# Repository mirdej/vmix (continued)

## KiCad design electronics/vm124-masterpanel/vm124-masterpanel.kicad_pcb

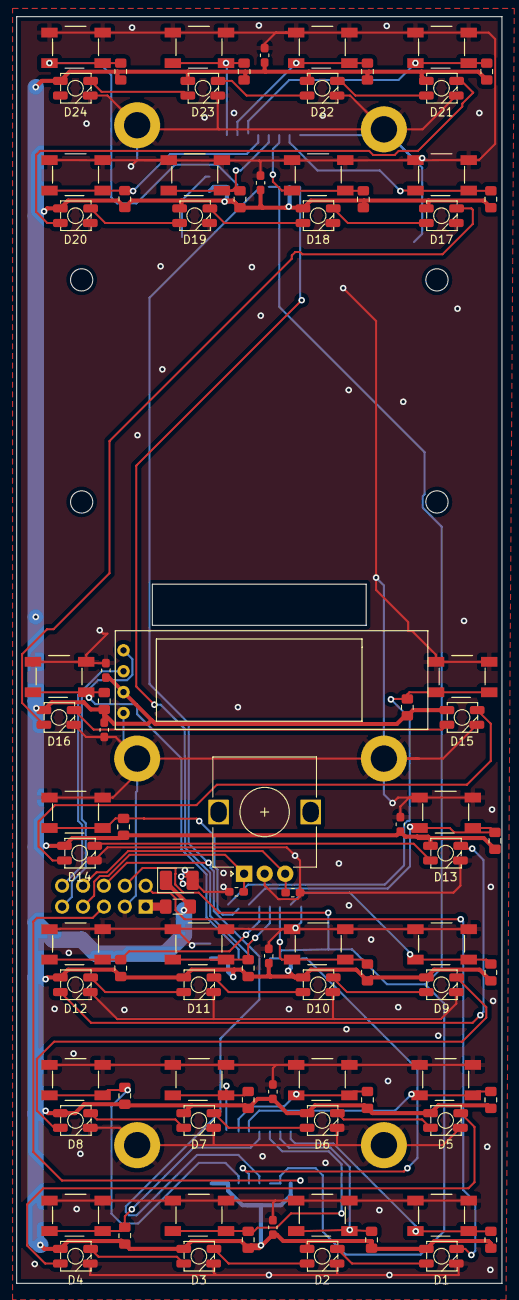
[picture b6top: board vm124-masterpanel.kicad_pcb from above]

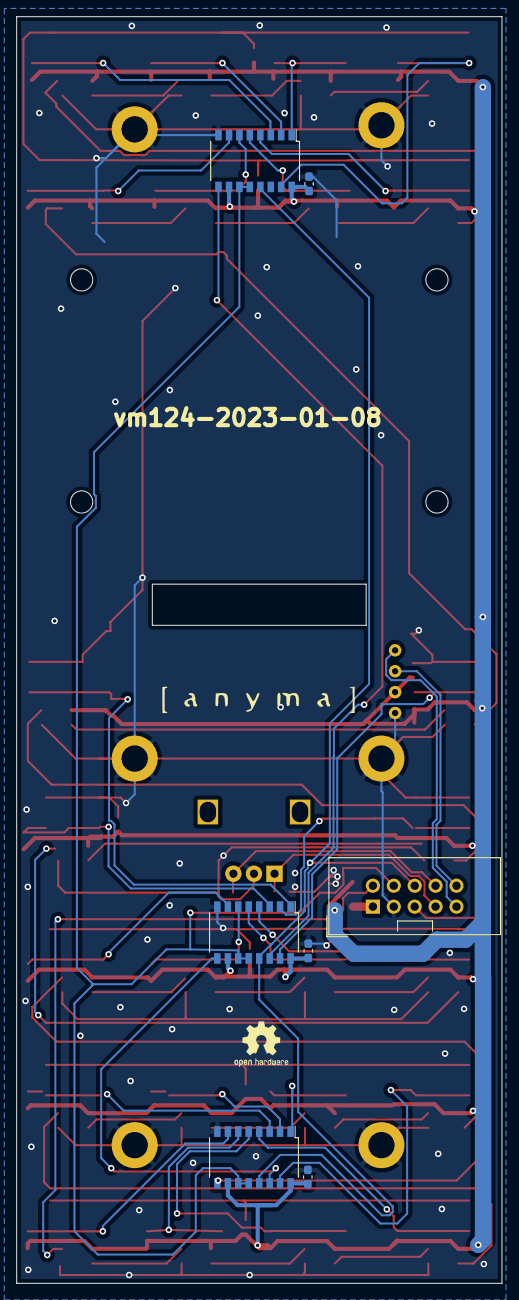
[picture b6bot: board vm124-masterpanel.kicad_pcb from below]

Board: 2 copper layers, 59.0 x 154.0 mm, 105 parts (9 on the bottom side), 60 nets.

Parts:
C1, C2, C3, C5, C6, C7, C8, C12, C13, C201, C202: C; C_0603_1608Metric_Pad1.05x0.95mm_HandSolder
C101: CP; CP_EIA-3528-21_Kemet-B_Pad1.50x2.35mm_HandSolder
C102, C103: 100n; C_0603_1608Metric_Pad1.05x0.95mm_HandSolder
D1, D2, D3, D4, D5, D6, D7, D8, D9, D10, D11, D12, D13, D14, D15, D16, D17, D18, D19, D20, D21, D22, D23, D24: SK6812MINI; SK6812-MINI-HS
FB101: Ferrite_Bead; L_1206_3216Metric_Pad1.42x1.75mm_HandSolder
H4, H5, H6, H7, H8, H9: MountingHole_Pad; MountingHole_3.2mm_M3_DIN965_Pad
H101, H102, H103, H104: MountingHole; MountingHole_2.7mm_M2.5
J101: Display; Bangood-OLED-128x32
J102: To-CPU; IDC-Header_2x05_P2.54mm_Vertical
R5, R6, R7, R8, R9, R10, R11, R12, R13, R14, R15, R16, R17, R18, R19, R20, R29, R30, R31, R32, R33, R34, R35, R36: R; R_0805_2012Metric_Pad1.15x1.40mm_HandSolder
SW5, SW6, SW7, SW8, SW9, SW10, SW11, SW12, SW13, SW14, SW15, SW16, SW17, SW18, SW19, SW20, SW29, SW30, SW31, SW32, SW33, SW34, SW35, SW36: SW_Push; Alps_Tactile_Switch
SW101: Rotary_Encoder; RotaryEncoder_Alps_EC12E_Vertical_H20mm
U2, U3, U5: 74LS597; SOP-16_4.4x10.4mm_P1.27mm
U101: LOGO; logo_anyma
U102: LOGO; OSHW-Logo2_7.3x6mm_SilkScreen

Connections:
/enc_a: C102.1, J102.7, SW101.A
/enc_b: C103.1, J102.8, SW101.B
/scl: J101.3, J102.10
/sda: J101.4, J102.9
GND: C1.2, C2.2, C3.2, C5.2, C6.2, C7.2, C8.2, C12.2, C13.2, C101.2, C102.2, C103.2, C201.2, C202.2, D1.2 (VSS), D2.2 (VSS), D3.2 (VSS), D4.2 (VSS), D5.2 (VSS), D6.2 (VSS), D7.2 (VSS), D8.2 (VSS), D9.2 (VSS), D10.2 (VSS), D11.2 (VSS), D12.2 (VSS), D13.2 (VSS), D14.2 (VSS), D15.2 (VSS), D16.2 (VSS), D17.2 (VSS), D18.2 (VSS), D19.2 (VSS), D20.2 (VSS), D21.2 (VSS), D22.2 (VSS), D23.2 (VSS), D24.2 (VSS), H4.1, H5.1, H6.1, H7.1, H8.1, H9.1, J101.1, J102.3, SW5.1, SW6.1, SW7.1, SW8.1, SW9.1, SW10.1, SW11.1, SW12.1, SW13.1, SW14.1, SW15.1, SW16.1, SW17.1, SW18.1, SW19.1, SW20.1, SW29.1, SW30.1, SW31.1, SW32.1, SW33.1, SW34.1, SW35.1, SW36.1, SW101.C, U2.8 (GND), U3.8 (GND), U5.8 (GND)
unnamed: D1.1 (DOUT), D2.3 (DIN)
unnamed: D2.1 (DOUT), D3.3 (DIN)
unnamed: D3.1 (DOUT), D4.3 (DIN)
unnamed: D4.1 (DOUT), D5.3 (DIN)
unnamed: D5.1 (DOUT), D6.3 (DIN)
unnamed: D6.1 (DOUT), D7.3 (DIN)
unnamed: D7.1 (DOUT), D8.3 (DIN)
unnamed: D8.1 (DOUT), D9.3 (DIN)
unnamed: D10.1 (DOUT), D11.3 (DIN)
unnamed: D9.1 (DOUT), D10.3 (DIN)
unnamed: D11.1 (DOUT), D12.3 (DIN)
unnamed: D12.1 (DOUT), D13.3 (DIN)
unnamed: D13.1 (DOUT), D14.3 (DIN)
unnamed: D14.1 (DOUT), D15.3 (DIN)
unnamed: D15.1 (DOUT), D16.3 (DIN)
unnamed: D16.1 (DOUT), D17.3 (DIN)
unnamed: D17.1 (DOUT), D18.3 (DIN)
unnamed: D18.1 (DOUT), D19.3 (DIN)
unnamed: D19.1 (DOUT), D20.3 (DIN)
unnamed: D20.1 (DOUT), D21.3 (DIN)
unnamed: D21.1 (DOUT), D22.3 (DIN)
unnamed: D22.1 (DOUT), D23.3 (DIN)
unnamed: D23.1 (DOUT), D24.3 (DIN)
unnamed: FB101.2, J102.1
unnamed: R5.2, SW5.2, U2.15 (A)
unnamed: R6.2, SW6.2, U2.1 (B)
unnamed: R7.2, SW7.2, U2.2 (C)
unnamed: R8.2, SW8.2, U2.3 (D)
unnamed: R9.2, SW9.2, U2.4 (E)
unnamed: R10.2, SW10.2, U2.5 (F)
unnamed: R11.2, SW11.2, U2.6 (G)
unnamed: R12.2, SW12.2, U2.7 (H)
unnamed: R13.2, SW13.2, U3.15 (A)
unnamed: R14.2, SW14.2, U3.1 (B)
unnamed: R15.2, SW15.2, U3.2 (C)
unnamed: R16.2, SW16.2, U3.3 (D)
unnamed: R17.2, SW17.2, U3.4 (E)
unnamed: R18.2, SW18.2, U3.5 (F)
unnamed: R19.2, SW19.2, U3.6 (G)
unnamed: R20.2, SW20.2, U3.7 (H)
unnamed: R29.2, SW29.2, U5.15 (A)
unnamed: R30.2, SW30.2, U5.1 (B)
unnamed: R31.2, SW31.2, U5.2 (C)
unnamed: R32.2, SW32.2, U5.3 (D)
unnamed: R33.2, SW33.2, U5.4 (E)
unnamed: R34.2, SW34.2, U5.5 (F)
unnamed: R35.2, SW35.2, U5.6 (G)
unnamed: R36.2, SW36.2, U5.7 (H)
unnamed: U2.9 (QH), U5.14 (SER)
unnamed: U3.14 (SER), U5.9 (QH)
VCC: C1.1, C2.1, C3.1, C5.1, C6.1, C7.1, C8.1, C12.1, C13.1, C101.1, C201.1, C202.1, D1.4 (VDD), D2.4 (VDD), D3.4 (VDD), D4.4 (VDD), D5.4 (VDD), D6.4 (VDD), D7.4 (VDD), D8.4 (VDD), D9.4 (VDD), D10.4 (VDD), D11.4 (VDD), D12.4 (VDD), D13.4 (VDD), D14.4 (VDD), D15.4 (VDD), D16.4 (VDD), D17.4 (VDD), D18.4 (VDD), D19.4 (VDD), D20.4 (VDD), D21.4 (VDD), D22.4 (VDD), D23.4 (VDD), D24.4 (VDD), FB101.1, J101.2, R5.1, R6.1, R7.1, R8.1, R9.1, R10.1, R11.1, R12.1, R13.1, R14.1, R15.1, R16.1, R17.1, R18.1, R19.1, R20.1, R29.1, R30.1, R31.1, R32.1, R33.1, R34.1, R35.1, R36.1, U2.10 (~R), U2.16 (VCC), U3.10 (~R), U3.16 (VCC), U5.10 (~R), U5.16 (VCC)
clk: J102.4, U2.11 (SCK), U2.12 (CLK), U3.11 (SCK), U3.12 (CLK), U5.11 (SCK), U5.12 (CLK)
cs: J102.6, U2.13 (~SLoad), U3.13 (~SLoad), U5.13 (~SLoad)
data: J102.5, U3.9 (QH)
pix: D1.3 (DIN), J102.2

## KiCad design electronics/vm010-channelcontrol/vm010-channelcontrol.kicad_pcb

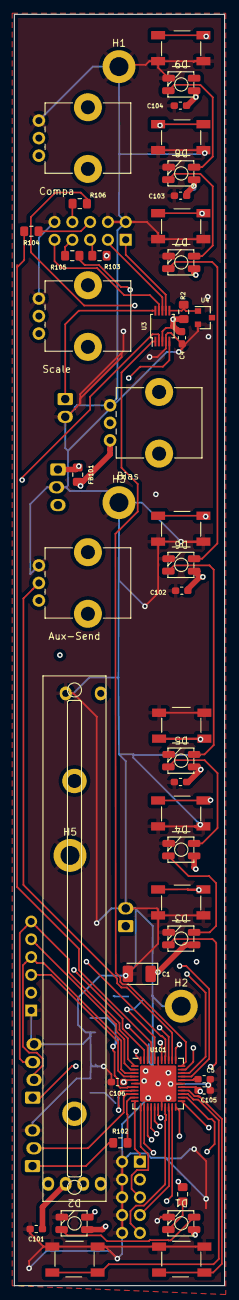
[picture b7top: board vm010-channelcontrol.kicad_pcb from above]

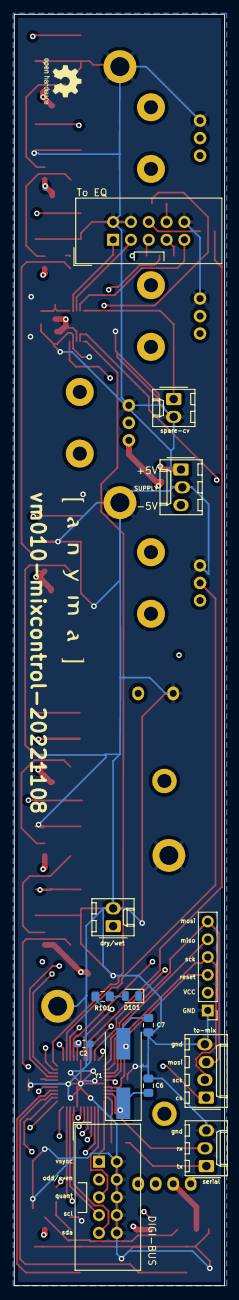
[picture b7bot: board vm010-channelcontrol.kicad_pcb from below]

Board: 4 copper layers, 30.0 x 181.4 mm, 64 parts (16 on the bottom side), 59 nets.

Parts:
C1: 10u; CP_EIA-3528-21_Kemet-B_Pad1.50x2.35mm_HandSolder
C2, C3, C4, C5, C101, C102, C103, C104, C105, C106: 100n; R_0603_1608Metric_Pad1.05x0.95mm_HandSolder
C6, C7: 10p; R_0805_2012Metric_Pad1.15x1.40mm_HandSolder
D1, D2, D3, D4, D5, D6, D7, D8, D9: SK6812MINI; SK6812-MINI-HS
D101: LED; LED_0805_2012Metric
FB101: Ferrite_Bead; L_0805_2012Metric_Pad1.15x1.40mm_HandSolder
H1, H2, H3, H5: MountingHole_Pad; MountingHole_2.7mm_M2.5_DIN965_Pad
J1: to-eq; IDC-Header_2x05_P2.54mm_Vertical
J3: Supply; Molex_KK-254_AE-6410-03A_1x03_P2.54mm_Vertical
J4, J5: Conn_01x02; Molex_KK-254_AE-6410-02A_1x02_P2.54mm_Vertical
J6: Conn_01x04; Molex_KK-254_AE-6410-04A_1x04_P2.54mm_Vertical
J101: Serial; Molex_KK-254_AE-6410-03A_1x03_P2.54mm_Vertical
J102: digitalbus; IDC-Header_2x05_P2.54mm_Vertical
R1, R102, R103, R104, R105, R106: 220; R_0805_2012Metric_Pad1.15x1.40mm_HandSolder
R2, R101: 560; R_0805_2012Metric_Pad1.15x1.40mm_HandSolder
RV1, RV2, RV3, RV5: R_POT; Potentiometer_Alps_RK09K_Single_Vertical
RV4: R_POT; Potentiometer_Alps_RS6011xP_Slide
SW1, SW2, SW3, SW4, SW5, SW6, SW7, SW8, SW9: SW_Push; Alps_Tactile_Switch
U1: AnymaISP; PinHeader_1x06_P2.54mm_Vertical
U3: MAX5741; MSOP-10_3x3mm_P0.5mm
U4: ADR510; SOT-23
U101: ATmega1284P-MU; QFN-44-1EP_7x7mm_P0.5mm_EP5.2x5.2mm
U102: LOGO; logo_anyma
U103: LOGO; OSHW-Logo2_7.3x6mm_SilkScreen
Y1: Crystal; Crystal_SMD_HC49-SD

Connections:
+5V: C4.1, FB101.2, J3.1, R2.1, U3.3 (VDD)
/aux-level: RV5.2, U101.35 (PA2|A2|26)
/bias-level: RV2.2, U101.30 (PA7|A7|31)
/bias_cv: J1.9, U3.9 (OUTC)
/bus_a: SW7.2, U101.16 (PD7|PWM|15)
/bus_b: SW8.2, U101.15 (PD6|PWM|14)
/bus_c: SW9.2, U101.14 (PD5|PWM|13)
/compa: SW2.2, U101.22 (PC3|TMS|19)
/compa-level: RV1.2, U101.31 (PA6|A6|30)
/compa_bypass: R104.2, U101.41 (PB1|1)
/compa_cv: J1.3, U3.8 (OUTB)
/dac2_select: J6.1, U101.32 (PA5|A5|29)
/dac_select: U3.1 (~CS), U101.33 (PA4|A4|28)
/drywet: SW4.2, U101.24 (PC5|TDI|21)
/edge_bypass: R103.2, U101.43 (PB3|PWM|AIN1|3)
/edges: SW1.2, U101.13 (PD4|PWM|12)
/extra_cv: J5.1, U3.10 (OUTD)
/invert: SW3.2, U101.23 (PC4|TDO|20)
/inverter_bypass: R105.2, U101.34 (PA3|A3|27)
/miso: U1.5 (MISO), U101.2 (PB6|PWM|MISO|6)
/mix-level: RV4.2, U101.36 (PA1|A1|25)
/mosi: J6.3, U1.6 (MOSI), U3.5 (DIN), U101.1 (PB5|MOSI|5)
/oddeven: J102.3, U101.21 (PC2TCK|18)
/pix: D1.3 (DIN), R1.1
/preview_bypass: J4.1, R106.2, U101.42 (PB2|INT2|AIN0|2)
/quantize_in: J102.5, U101.12 (PD3|TX1|INT1|11)
/rec|play|dub: SW5.2, U101.25 (PC6|22)
/reset: U1.3 (~RESET), U101.4 (~RESET)
/rx: J101.2, U101.9 (PD0|RX0|8)
/scale-level: RV3.2, U101.37 (PA0|A0|24)
/scale_cv: J1.1, U3.7 (OUTA)
/sck: J6.2, U1.4 (SCK), U3.2 (SCLK), U101.3 (PB7|PWM|SCK|7)
/scl: J102.9, U101.19 (PC0|SCL|16)
/sda: J102.7, U101.20 (PC1|SDA|17)
/stop|clear: SW6.2, U101.26 (PC7|23)
/tx: R102.2, U101.10 (PD1|TX0|9)
/vsync: J102.1, U101.11 (PD2|RX1|INT0|10)
GND: C1.2, C2.2, C3.2, C4.2, C5.2, C6.1, C7.2, C101.2, C102.2, C103.2, C104.2, C105.2, C106.2, D1.2 (VSS), D2.2 (VSS), D3.2 (VSS), D4.2 (VSS), D5.2 (VSS), D6.2 (VSS), D7.2 (VSS), D8.2 (VSS), D9.2 (VSS), D101.1 (K), H1.1, H2.1, H3.1, H5.1, J1.2, J1.4, J1.10, J3.2, J4.2, J5.2, J6.4, J101.3, J102.2, J102.4, J102.6, J102.8, J102.10, RV1.3, RV2.3, RV3.3, RV4.3, RV5.3, SW1.1, SW2.1, SW3.1, SW4.1, SW5.1, SW6.1, SW7.1, SW8.1, SW9.1, U1.1 (GND), U3.4 (GND), U4.2 (V-), U101.6 (GND), U101.18 (GND), U101.28 (GND), U101.39 (GND), U101.45 (GND)
unnamed: C5.1, U101.29 (AREF)
unnamed: C6.2, U101.8 (XTAL1), Y1.1
unnamed: C7.1, U101.7 (XTAL2), Y1.2
unnamed: D1.1 (DOUT), D2.3 (DIN)
unnamed: D2.1 (DOUT), D3.3 (DIN)
unnamed: D3.1 (DOUT), D4.3 (DIN)
unnamed: D4.1 (DOUT), D5.3 (DIN)
unnamed: D5.1 (DOUT), D6.3 (DIN)
unnamed: D6.1 (DOUT), D7.3 (DIN)
unnamed: D7.1 (DOUT), D8.3 (DIN)
unnamed: D8.1 (DOUT), D9.3 (DIN)
unnamed: D101.2 (A), R101.1
unnamed: J1.5, R103.1
unnamed: J1.6, R104.1
unnamed: J1.7, R105.1
unnamed: J1.8, R106.1
unnamed: J101.1, R102.1
unnamed: R1.2, U101.44 (PB4|PWM|SS|4)
unnamed: R2.2, U3.6 (REF), U4.1 (V+)
unnamed: R101.2, U101.40 (PB0|LED_BUILTIN|0)
VCC: C1.1, C2.1, C3.1, C101.1, C102.1, C103.1, C104.1, C105.1, C106.1, D1.4 (VDD), D2.4 (VDD), D3.4 (VDD), D4.4 (VDD), D5.4 (VDD), D6.4 (VDD), D7.4 (VDD), D8.4 (VDD), D9.4 (VDD), FB101.1, RV1.1, RV2.1, RV3.1, RV4.1, RV5.1, U1.2 (VCC), U101.5 (VCC), U101.17 (VCC), U101.27 (AVCC), U101.38 (VCC)

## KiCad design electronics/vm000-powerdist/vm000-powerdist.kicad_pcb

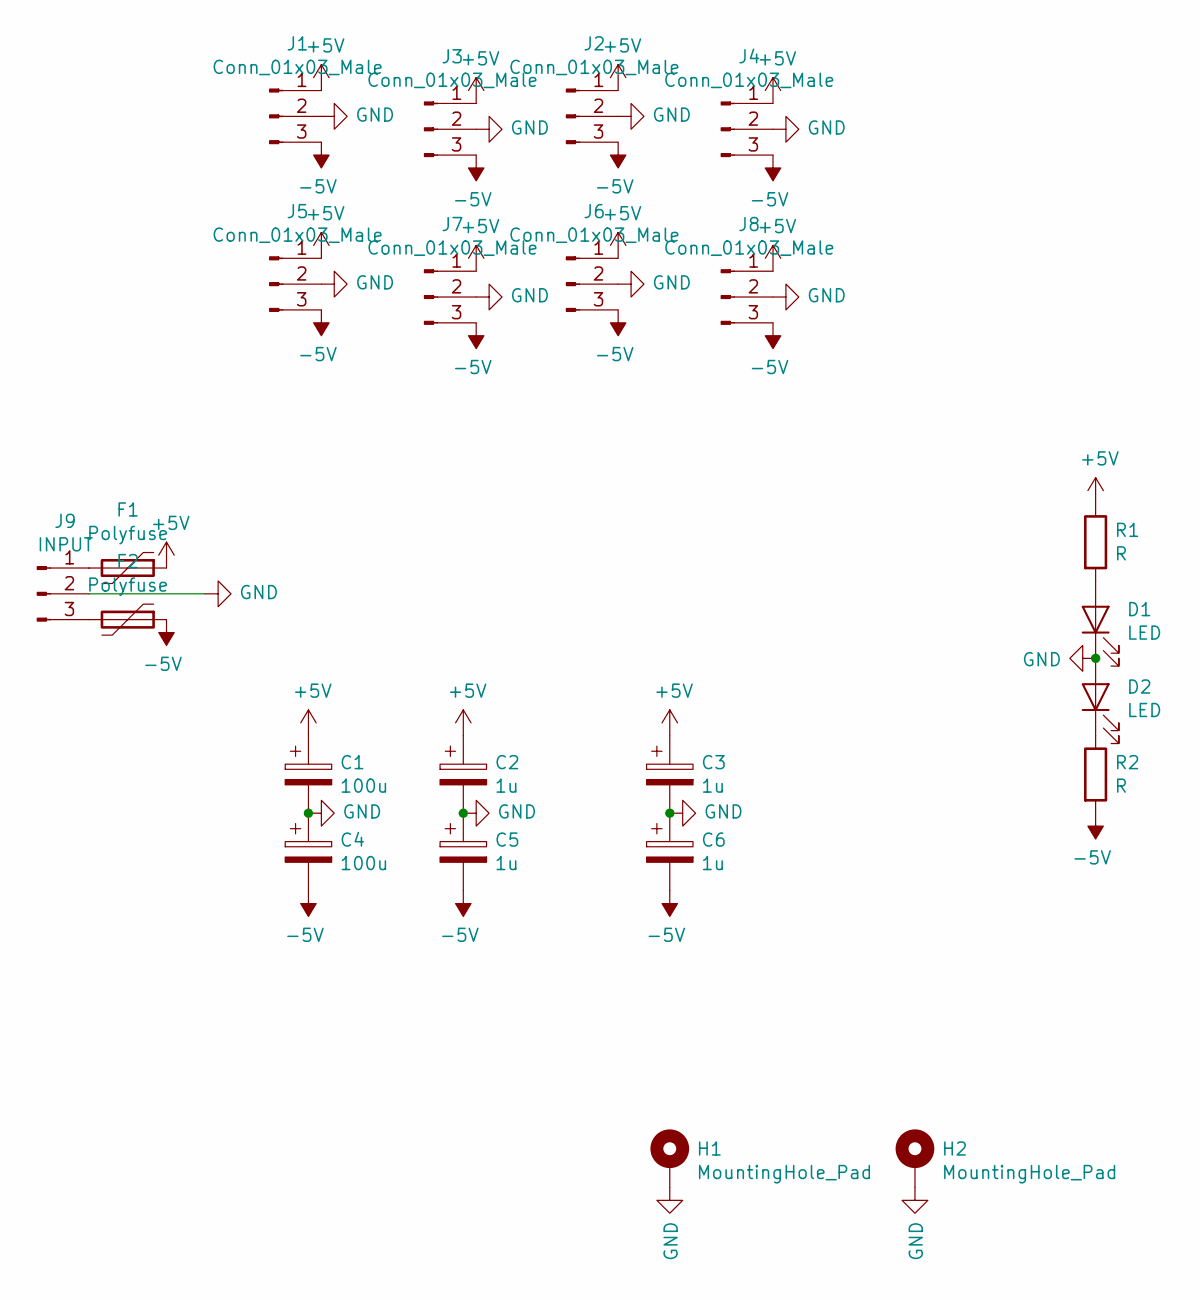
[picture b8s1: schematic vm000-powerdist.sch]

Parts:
C1, C4: 100u; CP_Radial_D10.0mm_P5.00mm
C2, C3, C5, C6: 1u; C_1206_3216Metric
D1, D2: LED; LED_0805_2012Metric_Pad1.15x1.40mm_HandSolder
F1, F2: Polyfuse; Fuse_0805_2012Metric_Pad1.15x1.40mm_HandSolder
H1, H2: MountingHole_Pad; MountingHole_3.2mm_M3_DIN965_Pad
J1, J2, J3, J4, J5, J6, J7, J8: Conn_01x03_Male; Molex_KK-254_AE-6410-03A_1x03_P2.54mm_Vertical
J9: INPUT; Molex_KK-254_AE-6410-03A_1x03_P2.54mm_Vertical
R1, R2: R; R_0805_2012Metric_Pad1.15x1.40mm_HandSolder

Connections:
+5V: C1.1, C2.1, C3.1, F1.1, J1.1, J2.1, J3.1, J4.1, J5.1, J6.1, J7.1, J8.1, R1.1
-5V: C4.2, C5.2, C6.2, F2.1, J1.3, J2.3, J3.3, J4.3, J5.3, J6.3, J7.3, J8.3, R2.2
GND: C1.2, C2.2, C3.2, C4.1, C5.1, C6.1, D1.1 (K), D2.2 (A), H1.1, H2.1, J1.2, J2.2, J3.2, J4.2, J5.2, J6.2, J7.2, J8.2, J9.2
unnamed: D1.2 (A), R1.2
unnamed: D2.1 (K), R2.1
unnamed: F1.2, J9.1
unnamed: F2.2, J9.3

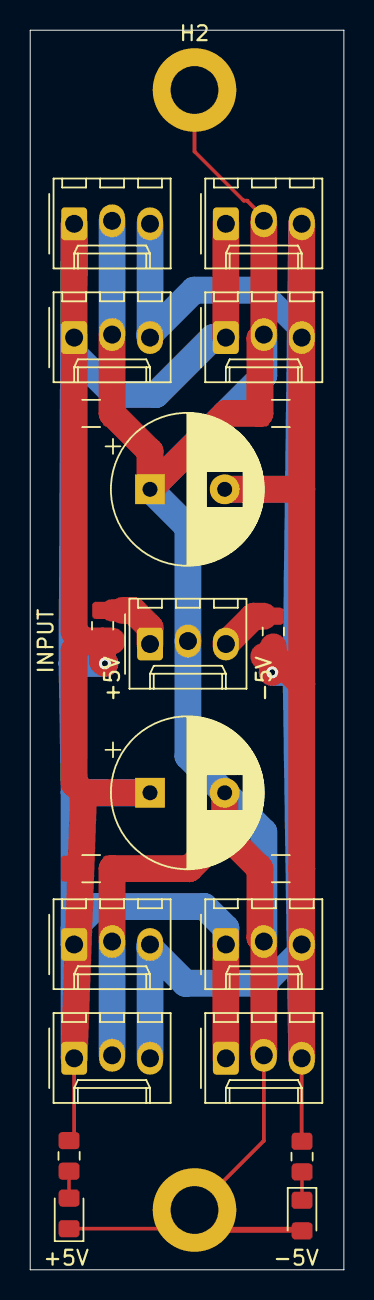
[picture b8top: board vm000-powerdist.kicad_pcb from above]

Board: 2 copper layers, 21.0 x 83.0 mm, 23 parts (0 on the bottom side), 7 nets.

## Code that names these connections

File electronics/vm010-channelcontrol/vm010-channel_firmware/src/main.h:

#ifndef __MAIN_INCLUDED__
#define __MAIN_INCLUDED__

#include "Arduino.h"

#define DEBUG 1

const int NUM_PIXELS = 9;
const int NUM_BTNS = 9;
const int NUM_POTS = 5;
const int NUM_CHAN = 8;

#define PIN_LED_BUILTIN 0
#define PIN_COMPA_OUT 1
#define PIN_PREVIEW_OUT 2
#define PIN_EDGES_OUT 3
#define PIN_PIXELS 4
#define PIN_MOSI 5
#define PIN_MISO 6
#define PIN_SCK 7

#define PIN_RX 8
#define PIN_TX 9
#define PIN_VSYNC 10
#define PIN_BEAT 11
#define PIN_BTN_EDGES 12
#define PIN_BTN_BUS_C 13
#define PIN_BTN_BUS_B 14
#define PIN_BTN_BUS_A 15

#define PIN_SCL 16
#define PIN_SDA 17
#define PIN_ODDEVEN 18
#define PIN_BTN_COMPA 19
#define PIN_BTN_INVERT 20
#define PIN_BTN_DRYWET 21
#define PIN_BTN_REC 22
#define PIN_BTN_STOP 23

#define PIN_AD_SCALE A0
#define PIN_AD_MIX A1
#define PIN_AD_AUX A2
#define PIN_INVERT_OUT 27
#define PIN_DAC0_CS 28
#define PIN_DAC1_CS 29
#define PIN_AD_COMPA A6
#define PIN_AD_BIAS A7

#define EEPROM_BUS_C 0
#define EEPROM_BUS_B 1
#define EEPROM_BUS_A 2
#define EEPROM_INVERT 3
#define EEPROM_COMPA 4
#define EEPROM_PFL 5
#define EEPROM_EDGES 6
#define EEPROM_I2C_ADDRESS 7


// scalke bias pots are inversed on board as of dec2020
const char PIN_POT[NUM_POTS] = {PIN_AD_BIAS, PIN_AD_COMPA, PIN_AD_SCALE, PIN_AD_AUX, PIN_AD_MIX};
const char PIN_BTN[NUM_BTNS] = {PIN_BTN_REC, PIN_BTN_STOP, PIN_BTN_BUS_C, PIN_BTN_BUS_B, PIN_BTN_BUS_A, PIN_BTN_DRYWET, PIN_BTN_INVERT, PIN_BTN_COMPA, PIN_BTN_EDGES};

#define LOOP_QUANTIZE 24 // quantize loop length to beat
                         // TODO: make this parameter selectable from vm129

#define LOOP_STATE_EMPTY 0
#define LOOP_STATE_REC 1
#define LOOP_STATE_DUB 2
#define LOOP_STATE_PLAY 3
#define LOOP_STATE_STOPPED 4
#define LOOP_STATE_REC_WAITING 5
#define LOOP_STATE_PLAY_WAITING 6

#define ERROR_NONE 0
#define ERROR_NO_BEAT 1
#define ERROR_NO_SYNC 2

#define BUTTON_COLOR CRGB(0, 5, 10)
#define SELECTION_COLOR CRGB::Gray

#define I2C_CALL_REC 0xF0
#define I2C_CALL_PLAY 0xF1
#define I2C_CALL_DUB 0xF2
#define I2C_CALL_STOP 0xF3
#define I2C_CALL_CLEAR 0xF4
#define I2C_CALL_STORE 0xB0
#define I2C_CALL_RECALL 0xB1
#define I2C_CALL_BRIGHTNESS 0xB2
#define I2C_CALL_VOLUME 0xC0
#define I2C_CALL_SET_CHAN 0xC1

#define BUS_A 6
#define BUS_B 5
#define BUS_C 4
#define BUS_D 3
#define SCALE 2
#define COMPA 1
#define BIAS 0
#endif

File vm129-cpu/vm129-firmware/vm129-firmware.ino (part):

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
const int PIN_ENCODER_A         = 36;
const int PIN_ENCODER_B         = 39;
const int PIN_HSYNC             = 34;
const int PIN_VSYNC             = 35;
const int PIN_MUX_3             = 32;
const int PIN_FOOTPEDAL         = 33;
const int PIN_FREE              = 25;
const int PIN_TRIGGER_IN        = 26;
const int PIN_BEATSYNC          = 27;
const int PIN_TRIGGER_3         = 14;
const int PIN_SYNKIETXT_EN      = 12;
const int PIN_PIXELS            = 13;

const int PIN_TRIGGER_2         = 15;
const int PIN_TRIGGER_1         = 02;
const int PIN_MUX_1             = 04;
const int PIN_VIDEO_READ        = 16;
const int PIN_SYNKIETXT         = 17;
const int PIN_BTN_LATCH         = 05;
const int PIN_BTN_CLK           = 18;
const int PIN_BTN_DATA          = 19;
const int PIN_SDA               = 21;
const int PIN_RX                = 03;
const int PIN_TX                = 01;
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//----------------------------------------------------------------------------------------
//																		set all trigger pins to low
void release_triggers() {
    digitalWrite(PIN_BEATSYNC, LOW);
    digitalWrite(PIN_TRIGGER_1, LOW);
    digitalWrite(PIN_TRIGGER_2, LOW);
    digitalWrite(PIN_TRIGGER_3, LOW);
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    buttons_raw = 0;
    
    SPI.beginTransaction(SPISettings(80000, LSBFIRST, SPI_MODE2));
    digitalWrite(PIN_BTN_LATCH,LOW);
    delayMicroseconds(100);
    digitalWrite(PIN_BTN_LATCH,HIGH);
    cli();
    for (int i = 0; i < NUM_REGISTERS; i++) {
        temp = ~SPI.transfer(0x00);
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	pixels[19-preview_out_channel] = preview_color;
	

    if (digitalRead(PIN_TRIGGER_1)) {pixels[22] = CRGB::Blue;}
    if (digitalRead(PIN_TRIGGER_2)) {pixels[21] = CRGB::Blue;}
    if (digitalRead(PIN_TRIGGER_3)) {pixels[20] = CRGB::Blue;}

	FastLED.show(); 
}
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        
        MIDI.sendRealTime(midi::Clock);

        if (tickCounter % beatclock_clocks == 0 ) digitalWrite(PIN_BEATSYNC, HIGH);
        if (tickCounter % trigger1_clocks == 0 ) digitalWrite(PIN_TRIGGER_1, HIGH);
        if (tickCounter % trigger2_clocks == 0 ) digitalWrite(PIN_TRIGGER_2, HIGH);
        if (tickCounter % trigger3_clocks == 0 ) digitalWrite(PIN_TRIGGER_3, HIGH);
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
    brightness = 100;

    FastLED.addLeds<NEOPIXEL, PIN_PIXELS>(pixels, NUM_PIXELS);
	FastLED.setBrightness(brightness);
	
	display.begin(SSD1306_SWITCHCAPVCC, 0x3C);
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    pinMode(PIN_TRIGGER_1, OUTPUT);
    pinMode(PIN_TRIGGER_2, OUTPUT);
    pinMode(PIN_TRIGGER_3, OUTPUT);
    pinMode(PIN_BEATSYNC, OUTPUT);
    pinMode(PIN_BTN_LATCH, OUTPUT);
    pinMode(PIN_RX, INPUT_PULLUP);   
    pinMode(PIN_MUX_1, OUTPUT);
    pinMode(PIN_MUX_2, OUTPUT);
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    preview_out_channel = 0;
    set_preview_mux();
    
    SPI.begin(PIN_BTN_CLK,PIN_BTN_DATA,PIN_FREE,PIN_BTN_LATCH);

    
 //   encoder.attachHalfQuad(PIN_ENCODER_B, PIN_ENCODER_A);
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
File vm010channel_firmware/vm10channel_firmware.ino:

//----------------------------------------------------------------------------------------
//
//	vm010  Firmware		
//						
//		Target MCU: ATMEGA88
//		Copyright:	2020 Michael Egger, me@anyma.ch
//		License: 	This is FREE software (as in free speech, not necessarily free beer)
//					published under gnu GPL v.3
//

// add || defined(__AVR_ATmega88__) to line 198 of fasled/platforms/avr/fastpin_avr.h

//----------------------------------------------------------------------------------------
#include <Timer.h>


#include "FastLED.h"

#define PIN_PIXELS PIN_PD7
#define PIN_EDGES   8
#define PIN_COMPA   9
#define PIN_INVERT  16

#define LOOP_STATE_EMPTY 0
#define LOOP_STATE_REC  1
#define LOOP_STATE_DUB  2
#define LOOP_STATE_PLAY     3
#define LOOP_STATE_STOPPED 4


const char	NUM_PIXELS				= 6;
const char	NUM_BTNS				= 6;

Timer t;
CRGB			pixels[NUM_PIXELS];
const char btn[NUM_BTNS] = {5,6,4,3,0,1};
char old_state[NUM_BTNS];
char loop_state;
char    pfl_state;
char    inverter_on;
char    compa_on;
char    edges_on;



void handle_rec_click() {
    switch (loop_state) { 
        case LOOP_STATE_EMPTY:
            loop_state = LOOP_STATE_REC;
            break;
         case LOOP_STATE_REC:
            loop_state = LOOP_STATE_PLAY;
            break;
         case LOOP_STATE_PLAY:
            loop_state = LOOP_STATE_DUB;
            break;
         case LOOP_STATE_DUB:
            loop_state = LOOP_STATE_PLAY;
            break;      
         case LOOP_STATE_STOPPED:
            loop_state = LOOP_STATE_PLAY;
            break;      
    }
}

void handle_stop_click() {
    switch (loop_state) { 
        case LOOP_STATE_EMPTY:
            loop_state = LOOP_STATE_EMPTY;
            break;
         case LOOP_STATE_REC:
            loop_state = LOOP_STATE_EMPTY;
            break;
         case LOOP_STATE_PLAY:
            loop_state = LOOP_STATE_STOPPED;
            break;
         case LOOP_STATE_DUB:
            loop_state = LOOP_STATE_STOPPED;
            break;
         case LOOP_STATE_STOPPED:
            loop_state = LOOP_STATE_EMPTY;
            break;      
    }
}


void update_leds(){
  	fill_solid(pixels, NUM_PIXELS, CRGB::Black);
    switch (loop_state) { 
        case LOOP_STATE_EMPTY:
            break;
         case LOOP_STATE_REC:
            pixels[0] = CRGB::Red;
            pixels[1] = CRGB::Red;
            break;
         case LOOP_STATE_PLAY:
            pixels[0] = CRGB::Green;
            pixels[1] = CRGB::Green;
            break;
         case LOOP_STATE_DUB:
            pixels[0] = CRGB::Orange;
            pixels[1] = CRGB::Orange;
            break;
         case LOOP_STATE_STOPPED:
            pixels[0] = CRGB::Yellow;
            pixels[1] = CRGB::Yellow;
            break;      
    
    }
    if (pfl_state) {pixels[2] = CRGB::Yellow;}
    if (inverter_on) {pixels[3] = CRGB::Yellow;}
    if (compa_on) {pixels[4] = CRGB::Yellow;}
    if (edges_on) {pixels[5] = CRGB::Yellow;}
    
    digitalWrite(PIN_INVERT, inverter_on);
    digitalWrite(PIN_COMPA, compa_on);
    digitalWrite(PIN_EDGES, edges_on);
    FastLED.show(); 
}

void check_btns() {
    char state;
 	for (int i = 0; i < NUM_BTNS; i++) {
 	    state = digitalRead(btn[i]);
 	    
 	    if (state != old_state[i]) {
 	        old_state[i] = state;
 	        if (!state) {
 	            switch (i) {
 	               case 0:
 	                    handle_rec_click();
 	                    break;
     	           case 1:
     	                handle_stop_click();
     	                break;
     	           case 2:
     	                pfl_state = ~pfl_state;
     	                break;
     	           case 3:
     	                inverter_on = ~inverter_on;
     	                break;
     	           case 4:
     	                compa_on = ~compa_on;
     	                break;
     	           case 5:
     	                edges_on = ~edges_on;
     	                break;
 	            }
 	            
 	            update_leds();
 	        }
 	    }
  	}
}

void setup() {
	FastLED.addLeds<SK6812, PIN_PIXELS, GRB>(pixels, NUM_PIXELS);
	  FastLED.setBrightness(50);

    for (int hue = 0; hue < 360; hue++) {
    	fill_rainbow( pixels, NUM_PIXELS, hue, 7);
	    delay(3);
    	FastLED.show(); 
  	}
  	
  	for (int i = 0; i < NUM_BTNS; i++) {
  	    pinMode(btn[i], INPUT_PULLUP);
  	}
  	
  	pinMode(PIN_INVERT, OUTPUT);
    pinMode(PIN_COMPA, OUTPUT);
    pinMode(PIN_EDGES, OUTPUT);

  	
  	fill_solid(pixels, NUM_PIXELS, CRGB::Black);
    FastLED.show(); 
    t.every(5,check_btns);

}

void loop() {
    t.update();
}

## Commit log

2020-08-20 add first modules
2020-08-20 info in readme
2020-08-20 add voltage divider at eq output
2020-08-21 new inverter, added edges
2020-08-25 add channel logic
2020-08-25 add firmware
2020-08-25 new version with scabi, ready for fab
2020-10-15 vm003-eq: corrected values to fix in/out impedance matching
2020-10-18 updated eq filter values
2020-11-06 vm003eq: cleanup schematics, multilayer board. vm001input modified microsynkie
2020-11-06 add power distribution
2020-11-06 multilayer vm001-input
2020-11-08 1 in 4 out mix module, multilayer pcb
2020-11-08 mixbus
2020-11-08 add cabling notes and flowchart
2020-11-13 vm10 with mega1284, multilayer, ready for fab
2020-11-17 change vias to 0.8/0.4
2020-11-21 better scabi range
2020-11-22 add dry/wet to eq bus, add current limiting resistors
2020-11-23 schematics of unified analog section
2020-11-23 board layout
2020-11-24 levelshifter for sync inputs, cut out active video portion of genlock, diode follower on audio sync in
2020-11-30 adapted (blindly) to new harware
2020-11-30 add 3d files
2020-11-30 add missing files
2020-11-30 more
2020-11-30 ignore dxf files
2020-12-01 beatsync automation. tested only in javascript simulator, not on actual hardware
2020-12-03 more gain in mixr
2020-12-03 gnd issing on genlock mux
2020-12-05 add testing firmware
2020-12-08 correct dry/wet sync and burst resyncing. clean up layout
2020-12-08 add some 3d files
2020-12-08 add mixer testrig
2020-12-14 store button state in eeprom
2020-12-14 add i2c stub. only brightness implemented
2020-12-27 compa more black
2020-12-28 add vm020
2020-12-28 vm20-output: new low clip
2020-12-29 nex gen architecture. input/mixer/output schematic
2021-01-01 vm101 board layout
2021-01-02 add master faders
2021-01-03 add umcc connectors. close jumper for fcc shield to eq
2021-01-03 silk
2021-01-03 add umcc
2021-01-03 ne version of cpu. bnc input, umcc out. recreation of genlock signal
2021-01-03 varios sketchup files
2021-01-03 add frontpanel buttons
2021-01-03 silkscreen
2021-01-04 connect missing nets. flip fcc connector
2021-01-04 ready for fab
2021-01-17 add latest firmware
2021-01-18 buttons, leds and basic menus
2021-01-21 attempt to better clamp genlock input with lt1228. lots of ringing
2021-02-03 correct bat54 footprint. non log scale input
2021-02-03 try correct resync impedance. add synkietxt input
2021-02-04 add bias-bias
2021-02-04 add gndjumpers. production ready
2021-02-05 new clamp, synkietxt. reeady for fab
2021-02-05 add preview switch
2021-02-12 mod for better burst
2021-02-14 first image
2021-02-14 fix link
2021-03-14 version before going to langenthal
2021-03-14 add sketchup files
2021-03-28 add documentation
2021-03-28 try to get link work
2021-03-28 try to fix links
2021-03-29 some more text and images
2021-04-03 cleaning up
2021-04-03 add untracked files
2021-04-03 more cleanup
2021-04-03 add architecture overview
2021-04-04 add description of master section
2021-04-07 add link to build blog
2022-08-29 add gain to videoinput to have 0-1V range (synkie style). kicad6
2022-11-08 update to kicad 6. change sk6812 to hand solder version
2022-11-08 update to 6.0. change footprints to sk6812-hs
2022-11-08 update silkscreen
2022-12-02 fix automation reording
2022-12-02 add overdub
2023-01-02 add comment about scaling back PFL levels before resyncing
2023-01-08 change neopixel to handsolder version
2023-01-30 correct burst gain on genlock out
2023-01-30 add buffers, change to esp32-s3
2023-01-31 add vm130 audio out
2023-01-31 vm129 new board layout
2023-02-25 move to platformio, esp32-s3
2023-02-25 adapted to s3,new layout. compiles
2023-03-04 Firmware for ESP32-S3 version feb 2023
2023-03-22 esp32 s3 version
2023-03-22 add bom
2023-05-01 correct connections and resistor values for 3.3V MIDI
2023-08-29 genlock on umcc
2024-07-15 move to platformio
2024-07-15 remove compile errords
2024-11-23 add fuses
2024-11-24 refactor
2024-12-05 apple midi channel control
